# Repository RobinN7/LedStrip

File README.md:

# LedStrip

RGB LED strip control project, experimented on many platforms with various interfaces

## Python :

*Source: Python folder*

## PIC :

*Source: LedStrip.X folder*

Full 18F26K80 code, different features available :

* Manual colors
* Music follower
* Strobe

PWM documentation : Datasheet page 262

## Arduino : 

*Source: LedStrip.ino script*

Simple code to receive data from PC and generate RGB PWMs

## Android : 

### Network socket : 

*Source: LedStrips folder*

### Bluetooth link : 

*Source: LedStrips_BT folder*

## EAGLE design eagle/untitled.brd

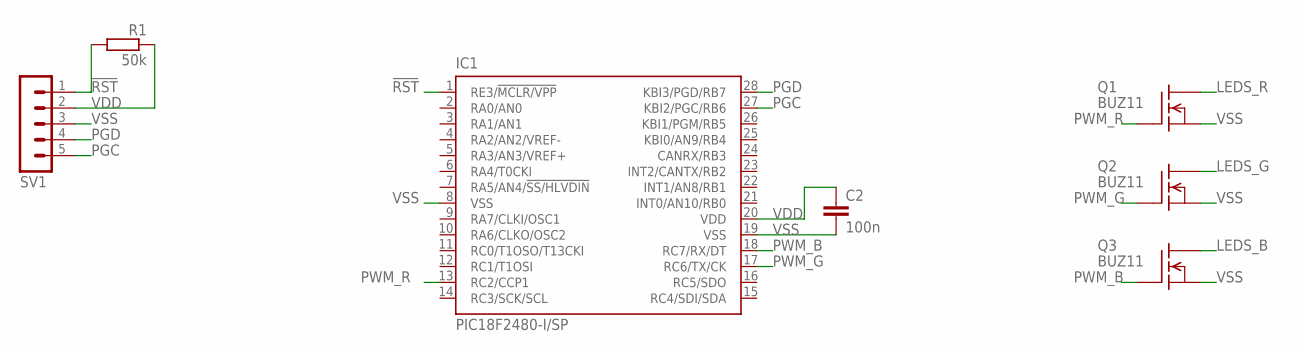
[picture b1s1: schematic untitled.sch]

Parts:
C2: 100n; C050-024X044
IC1: PIC18F2480-I/SP; DIL28-3
Q1, Q2, Q3: BUZ11; TO220
R1: 50k; 0207/10
SV1: MA05-1

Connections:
!RST: IC1.1 (RE3/!MCLR/VPP), R1.2, SV1.1
LEDS_B: Q3.2 (D)
LEDS_G: Q2.2 (D)
LEDS_R: Q1.2 (D)
PGC: IC1.27 (KBI2/PGC/RB6), SV1.5
PGD: IC1.28 (KBI3/PGD/RB7), SV1.4
PWM_B: IC1.18 (RC7/RX/DT), Q3.1 (G)
PWM_G: IC1.17 (RC6/TX/CK), Q2.1 (G)
PWM_R: IC1.13 (RC2/CCP1), Q1.1 (G)
VDD: C2.1, IC1.20 (VDD), R1.1, SV1.2
VSS: C2.2, IC1.8 (VSS), IC1.19 (VSS), Q1.3 (S), Q2.3 (S), Q3.3 (S), SV1.3

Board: 2 copper layers, 7 parts (0 on the bottom side), 8 nets, no tracks yet.

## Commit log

2015-03-01 first working code
2015-03-16 code final
2015-03-16 dimm function
2015-03-24 working real time FFT on PA stream
2015-04-03 commit de sécurité
2015-04-16 datasheet
2015-04-22 Ça marche du premier coup ! :D
2015-04-24 rx fonctionnel
2015-04-24 guirlande fonctionnelle sur PIC
2015-04-24 oh oui ca marche
2015-04-25 ADC qui marche
2015-04-25 colors on potentiometers
2015-04-25 correction petit bug
2015-05-18 ajout code sur PIC fonctionnel
2015-05-19 Ajout mode hors ligne RGB aux potars
2015-05-23 gestion des priorités d'interruptions
2015-05-23 add documentation
2015-05-23 timer0 calibration 1ms
2015-05-24 add palkeo code, strobe mode
2015-05-27 ajout socket python
2015-06-29 mode musique par défaut
2015-06-30 Application android pour accès bluetooth sur le contrôleur
2015-07-01 linear layout, no longer crashing on pause, frequency plot frame
2015-07-02 nice frequency analysis plot
2015-07-07 ajout barre de sensibilité micro
2015-07-10 Choix colorwheel/audioanalysis
2015-07-11 smoothness adjustability
2015-07-24 some changes
2015-07-26 add eagle PCB files
2015-07-26 eagle update
